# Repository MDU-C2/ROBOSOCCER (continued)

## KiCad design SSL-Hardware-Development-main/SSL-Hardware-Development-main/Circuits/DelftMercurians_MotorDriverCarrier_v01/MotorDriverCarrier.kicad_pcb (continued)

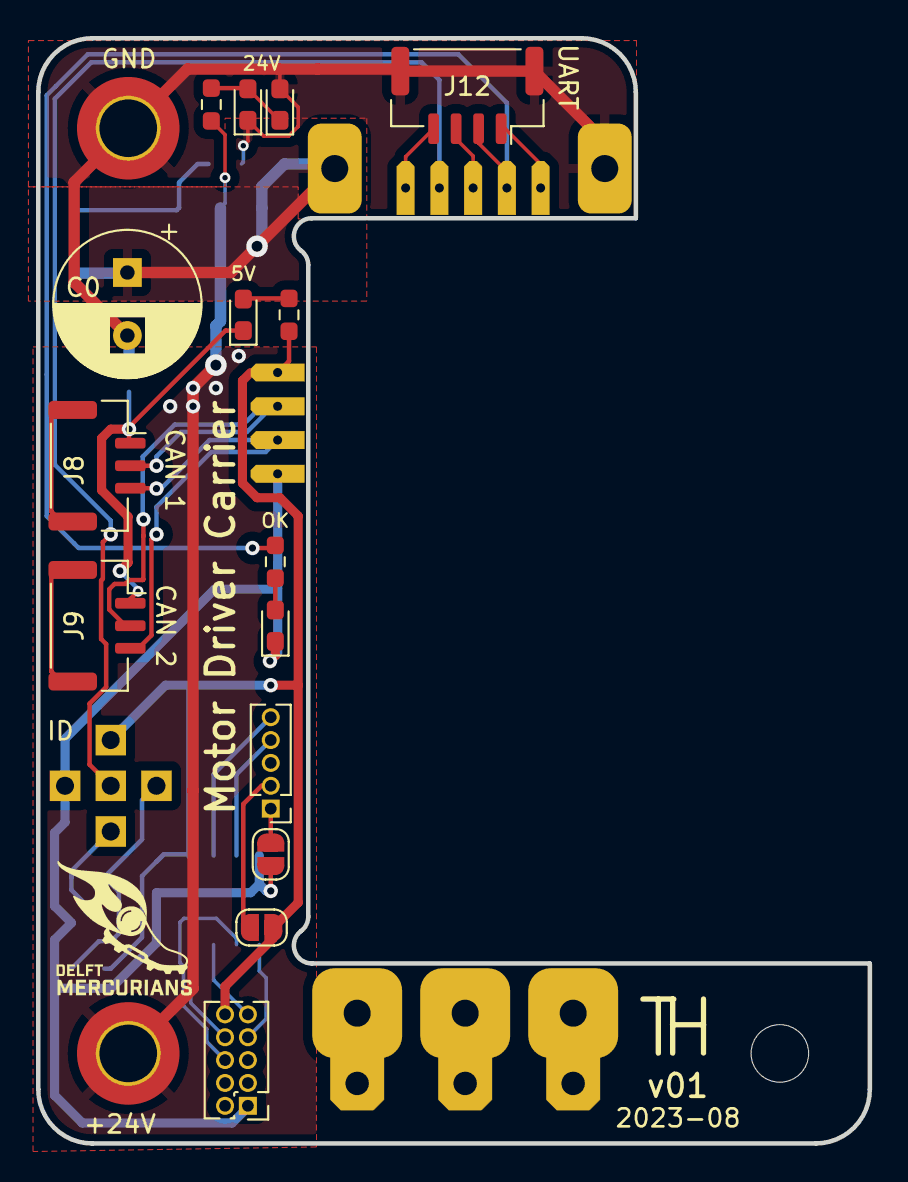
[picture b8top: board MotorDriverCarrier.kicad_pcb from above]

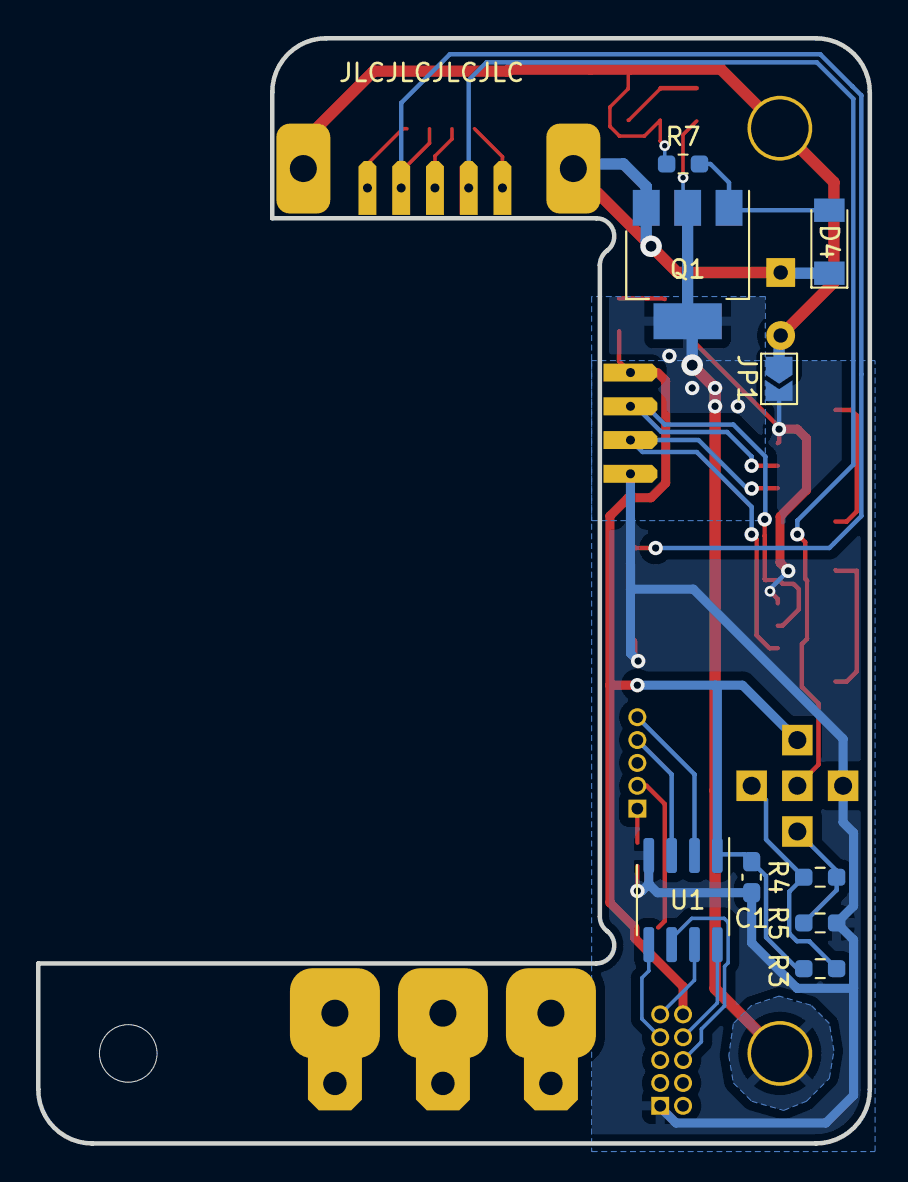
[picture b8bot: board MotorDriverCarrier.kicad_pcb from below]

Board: 2 copper layers, 46.2 x 61.4 mm, 36 parts (10 on the bottom side), 26 nets.

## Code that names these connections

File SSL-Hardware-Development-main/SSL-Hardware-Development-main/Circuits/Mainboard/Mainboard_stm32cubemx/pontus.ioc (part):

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Mcu.Name=STM32H723ZGTx
Mcu.Package=LQFP144
Mcu.UserName=STM32H723ZGTx
PA0.GPIOParameters=GPIO_Label
PA0.GPIO_Label=M1_PWM
PA0.Signal=S_TIM5_CH1
PA1.GPIOParameters=GPIO_Label
PA1.GPIO_Label=M1_Encoder_B
PA1.Signal=S_TIM2_CH2
PA10.GPIOParameters=GPIO_Label
PA10.GPIO_Label=USB_FS_ID
PA10.Mode=OTG/Dual-Role-Device-FS
PA10.Signal=USB_OTG_HS_ID
PA11.GPIOParameters=GPIO_Label
PA11.GPIO_Label=USB_FS_DM
PA11.Mode=OTG/Dual-Role-Device-FS
PA11.Signal=USB_OTG_HS_DM
PA12.GPIOParameters=GPIO_Label
PA12.GPIO_Label=USB_FS_DP
PA12.Mode=OTG/Dual-Role-Device-FS
PA12.Signal=USB_OTG_HS_DP
PA13(JTMS/SWDIO).GPIOParameters=GPIO_Label
PA13(JTMS/SWDIO).GPIO_Label=SWDIO
PA13(JTMS/SWDIO).Mode=Trace_Asynchronous_SW
PA13(JTMS/SWDIO).Signal=DEBUG_JTMS-SWDIO
PA14(JTCK/SWCLK).GPIOParameters=GPIO_Label
PA14(JTCK/SWCLK).GPIO_Label=SWCLK
PA14(JTCK/SWCLK).Mode=Trace_Asynchronous_SW
PA14(JTCK/SWCLK).Signal=DEBUG_JTCK-SWCLK
PA15(JTDI).GPIOParameters=GPIO_Label
PA15(JTDI).GPIO_Label=M1_Encoder_A
PA15(JTDI).Signal=S_TIM2_CH1_ETR
PA2.GPIOParameters=GPIO_Label
PA2.GPIO_Label=M2_TX
PA2.Mode=Asynchronous
PA2.Signal=USART2_TX
PA3.GPIOParameters=GPIO_Label
PA3.GPIO_Label=M2_RX
PA3.Mode=Asynchronous
PA3.Signal=USART2_RX
PA4.GPIOParameters=GPIO_Label
PA4.GPIO_Label=WSENS_CS
PA4.Signal=GPIO_Output
PA5.GPIOParameters=GPIO_Label
PA5.GPIO_Label=WSENS_SCL
PA5.Mode=Full_Duplex_Master
PA5.Signal=SPI1_SCK
PA6.GPIOParameters=GPIO_Label
PA6.GPIO_Label=WSENS_SAO
PA6.Mode=Full_Duplex_Master
PA6.Signal=SPI1_MISO
PA7.GPIOParameters=GPIO_Label
PA7.GPIO_Label=RMII_CRS_DV
PA7.Signal=ETH_CRS_DV
PA8.GPIOParameters=GPIO_Label
PA8.GPIO_Label=VL6180_SCL
PA8.Mode=I2C
PA8.Signal=I2C3_SCL
PA9.GPIOParameters=GPIO_Label
PA9.GPIO_Label=USB_FS_VBUS
PA9.Mode=Activate_VBUS_FS
PA9.Signal=USB_OTG_HS_VBUS
PB0.GPIOParameters=GPIO_Label
PB0.GPIO_Label=LED_GREEN
PB0.Signal=GPIO_Output
PB10.GPIOParameters=GPIO_Label
PB10.GPIO_Label=VL53L4CD_SCL
PB10.Mode=I2C
PB10.Signal=I2C2_SCL
PB11.GPIOParameters=GPIO_Label
PB11.GPIO_Label=VL53L4CD_SDA
PB11.Mode=I2C
PB11.Signal=I2C2_SDA
PB12.GPIOParameters=GPIO_Label
PB12.GPIO_Label=Rpi_RX
PB12.Mode=Asynchronous
PB12.Signal=UART5_RX
PB13.GPIOParameters=GPIO_Label
PB13.GPIO_Label=RMII_TXD1
PB13.Signal=ETH_TXD1
PB14.GPIOParameters=GPIO_Label
PB14.GPIO_Label=M5_PWM
PB14.Signal=S_TIM12_CH1
PB15.GPIOParameters=GPIO_Label
PB15.GPIO_Label=M1_RX
PB15.Mode=Asynchronous
PB15.Signal=USART1_RX
PB3(JTDO/TRACESWO).GPIOParameters=GPIO_Label
PB3(JTDO/TRACESWO).GPIO_Label=SWO
PB3(JTDO/TRACESWO).Mode=Trace_Asynchronous_SW
PB3(JTDO/TRACESWO).Signal=DEBUG_JTDO-SWO
PB4(NJTRST).GPIOParameters=GPIO_Label
PB4(NJTRST).GPIO_Label=M2_Encoder_A
PB4(NJTRST).Signal=S_TIM3_CH1
PB5.GPIOParameters=GPIO_Label
PB5.GPIO_Label=M2_Encoder_B
PB5.Signal=S_TIM3_CH2
PB6.GPIOParameters=GPIO_Label
PB6.GPIO_Label=M1_TX
PB6.Mode=Asynchronous
PB6.Signal=USART1_TX
PB7.GPIOParameters=GPIO_Label
PB7.GPIO_Label=M3_Encoder_B
PB7.Signal=S_TIM4_CH2
PB8.GPIOParameters=GPIO_Label
PB8.GPIO_Label=SEN0374_SCL
PB8.Mode=I2C
PB8.Signal=I2C1_SCL
PB9.GPIOParameters=GPIO_Label
PB9.GPIO_Label=SEN0374_SDA
PB9.Mode=I2C
PB9.Signal=I2C1_SDA
PC1.GPIOParameters=GPIO_Label
PC1.GPIO_Label=RMII_MDC
PC1.Signal=ETH_MDC
PC10.GPIOParameters=GPIO_Label
PC10.GPIO_Label=M5_TX
PC10.Mode=Asynchronous
PC10.Signal=UART4_TX
PC11.GPIOParameters=GPIO_Label
PC11.GPIO_Label=M5_RX
PC11.Mode=Asynchronous
PC11.Signal=UART4_RX
PC12.GPIOParameters=GPIO_Label
PC12.GPIO_Label=Rpi_TX
PC12.Mode=Asynchronous
PC12.Signal=UART5_TX
PC13.GPIOParameters=GPIO_Label
PC13.GPIO_Label=B1 (Blue_User_Button)
PC13.Signal=GPIO_Input
PC14-OSC32_IN.Mode=LSE-External-Oscillator
PC14-OSC32_IN.Signal=RCC_OSC32_IN
PC15-OSC32_OUT.Mode=LSE-External-Oscillator
PC15-OSC32_OUT.Signal=RCC_OSC32_OUT
PC2_C.GPIOParameters=GPIO_Label
PC2_C.GPIO_Label=RF_MISO
PC2_C.Mode=Full_Duplex_Master
PC2_C.Signal=SPI2_MISO
PC3_C.GPIOParameters=GPIO_Label
PC3_C.GPIO_Label=RF_MOSI
PC3_C.Mode=Full_Duplex_Master
PC3_C.Signal=SPI2_MOSI
PC4.GPIOParameters=GPIO_Label
PC4.GPIO_Label=RMII_RXD0
PC4.Signal=ETH_RXD0
PC5.GPIOParameters=GPIO_Label
PC5.GPIO_Label=RMII_RXD1
PC5.Signal=ETH_RXD1
PC6.GPIOParameters=GPIO_Label
PC6.GPIO_Label=M4_Encoder_A
PC6.Signal=S_TIM8_CH1
PC7.GPIOParameters=GPIO_Label
PC7.GPIO_Label=M4_Encoder_B
PC7.Signal=S_TIM8_CH2
PC8.GPIOParameters=GPIO_Label
PC8.GPIO_Label=VL6180_IO0
PC8.Signal=GPIO_Output
PC9.GPIOParameters=GPIO_Label
PC9.GPIO_Label=VL6180_SDA
PC9.Mode=I2C
PC9.Signal=I2C3_SDA
PD10.Signal=GPIO_Output
PD12.GPIOParameters=GPIO_Label
PD12.GPIO_Label=M3_Encoder_A
PD12.Signal=S_TIM4_CH1
PD13.GPIOParameters=GPIO_Label
PD13.GPIO_Label=SEN0374_INT
PD13.Signal=GPIO_Output
PD14.GPIOParameters=GPIO_Label
PD14.GPIO_Label=SEN0374_Boot
PD14.Signal=GPIO_Output
PD15.GPIOParameters=GPIO_Label
PD15.GPIO_Label=SEN0374_PS1
PD15.Signal=GPIO_Output
PD3.GPIOParameters=GPIO_Label
PD3.GPIO_Label=RF_SCK
PD3.Mode=Full_Duplex_Master
PD3.Signal=SPI2_SCK
PD7.GPIOParameters=GPIO_Label
PD7.GPIO_Label=WSENS_SDA
PD7.Mode=Full_Duplex_Master
PD7.Signal=SPI1_MOSI
PD8.GPIOParameters=GPIO_Label
PD8.GPIO_Label=STLK_VCP_RX
PD8.Mode=Asynchronous
PD8.Signal=USART3_TX
PD9.GPIOParameters=GPIO_Label
PD9.GPIO_Label=STLK_VCP_TX
PD9.Mode=Asynchronous
PD9.Signal=USART3_RX
PE1.GPIOParameters=GPIO_Label
PE1.GPIO_Label=LED_YELLOW
PE1.Signal=GPIO_Output
PE15.GPIOParameters=GPIO_Label
PE15.GPIO_Label=RF_CS
PE15.Signal=GPIO_Output
PE2.GPIOParameters=GPIO_Label
PE2.GPIO_Label=M4_RX
PE2.Mode=Asynchronous
PE2.Signal=USART10_RX
PE3.GPIOParameters=GPIO_Label
PE3.GPIO_Label=M4_TX
PE3.Mode=Asynchronous
PE3.Signal=USART10_TX
PE5.GPIOParameters=GPIO_Label
PE5.GPIO_Label=M2_PWM
PE5.Signal=S_TIM15_CH1
PF0.GPIOParameters=GPIO_Label
PF0.GPIO_Label=VL53L4CD2_SDA
PF0.Mode=I2C
PF0.Signal=I2C5_SDA
PF1.GPIOParameters=GPIO_Label
PF1.GPIO_Label=VL53L4CD2_SCL
PF1.Mode=I2C
PF1.Signal=I2C5_SCL
PF11.GPIOParameters=GPIO_Label
PF11.GPIO_Label=M4_PWM
PF11.Mode=PWM_Input_1
PF11.Signal=TIM24_CH1
PF14.GPIOParameters=GPIO_Label
PF14.GPIO_Label=ADPS-9960_SCL
PF14.Mode=I2C
PF14.Signal=I2C4_SCL
PF15.GPIOParameters=GPIO_Label
PF15.GPIO_Label=ADPS-9960_SDA
PF15.Mode=I2C
PF15.Signal=I2C4_SDA
PF2.GPIOParameters=GPIO_Label
PF2.GPIO_Label=VL53L4CD_SHUT
PF2.Signal=GPIO_Output
PF3.GPIOParameters=GPIO_Label
PF3.GPIO_Label=VL53L4CD_INT
PF3.Signal=GPIO_Output
PF4.GPIOParameters=GPIO_Label
PF4.GPIO_Label=VL53L4CD2_INT
PF4.Signal=GPIO_Output
PF5.GPIOParameters=GPIO_Label
PF5.GPIO_Label=VL53L4CD2_SHUT
PF5.Signal=GPIO_Output
PF6.GPIOParameters=GPIO_Label
PF6.GPIO_Label=M3_PWM
PF6.Mode=PWM_Input_1
PF6.Signal=TIM23_CH1
PG11.GPIOParameters=GPIO_Label
PG11.GPIO_Label=RMII_TX_EN
PG11.Signal=ETH_TX_EN
PG13.GPIOParameters=GPIO_Label
PG13.GPIO_Label=RMII_TXD0
PG13.Signal=ETH_TXD0
PG14.GPIOParameters=GPIO_Label
PG14.GPIO_Label=M3_TX
PG14.Mode=Asynchronous
PG14.Signal=USART6_TX
PG2.GPIOParameters=GPIO_Label
PG2.GPIO_Label=SEN0374_PS2
PG2.Signal=GPIO_Output
PG3.GPIOParameters=GPIO_Label
PG3.GPIO_Label=SEN0374_BL-IND
PG3.Signal=GPIO_Output
PG4.GPIOParameters=GPIO_Label
PG4.GPIO_Label=SEN0374_RST
PG4.Signal=GPIO_Output
PG5.Signal=GPIO_Output
PG6.GPIOParameters=GPIO_Label
PG6.GPIO_Label=ADPS-9960_INT
PG6.Signal=GPIO_Output
PG7.GPIOParameters=GPIO_Label
PG7.GPIO_Label=USB_FS_OVCR
PG7.Signal=GPXTI7
PG8.GPIOParameters=GPIO_Label
PG8.GPIO_Label=VL6180_IO1
PG8.Signal=GPIO_Output
PG9.GPIOParameters=GPIO_Label
PG9.GPIO_Label=M3_RX
PG9.Mode=Asynchronous
PG9.Signal=USART6_RX
PH0-OSC_IN.GPIOParameters=GPIO_Label
PH0-OSC_IN.GPIO_Label=MCO
PH0-OSC_IN.Mode=HSE-External-Oscillator
PH0-OSC_IN.Signal=RCC_OSC_IN
PH1-OSC_OUT.Mode=HSE-External-Oscillator
PH1-OSC_OUT.Signal=RCC_OSC_OUT
RCC.HSE_VALUE=8000000
RCC.SYSCLKFreq_VALUE=550000000
RCC.SYSCLKSource=RCC_SYSCLKSOURCE_PLLCLK
board=NUCLEO-H723ZG
boardIOC=true

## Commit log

2025-01-29 fixed all our repos into this one repo and fixed main readme file
2025-01-31 removing git submodules
2025-01-31 added copies of each repo
2025-01-31 added wiki
2025-01-31 latest version of the repos
2025-01-31 removed unintentional file
